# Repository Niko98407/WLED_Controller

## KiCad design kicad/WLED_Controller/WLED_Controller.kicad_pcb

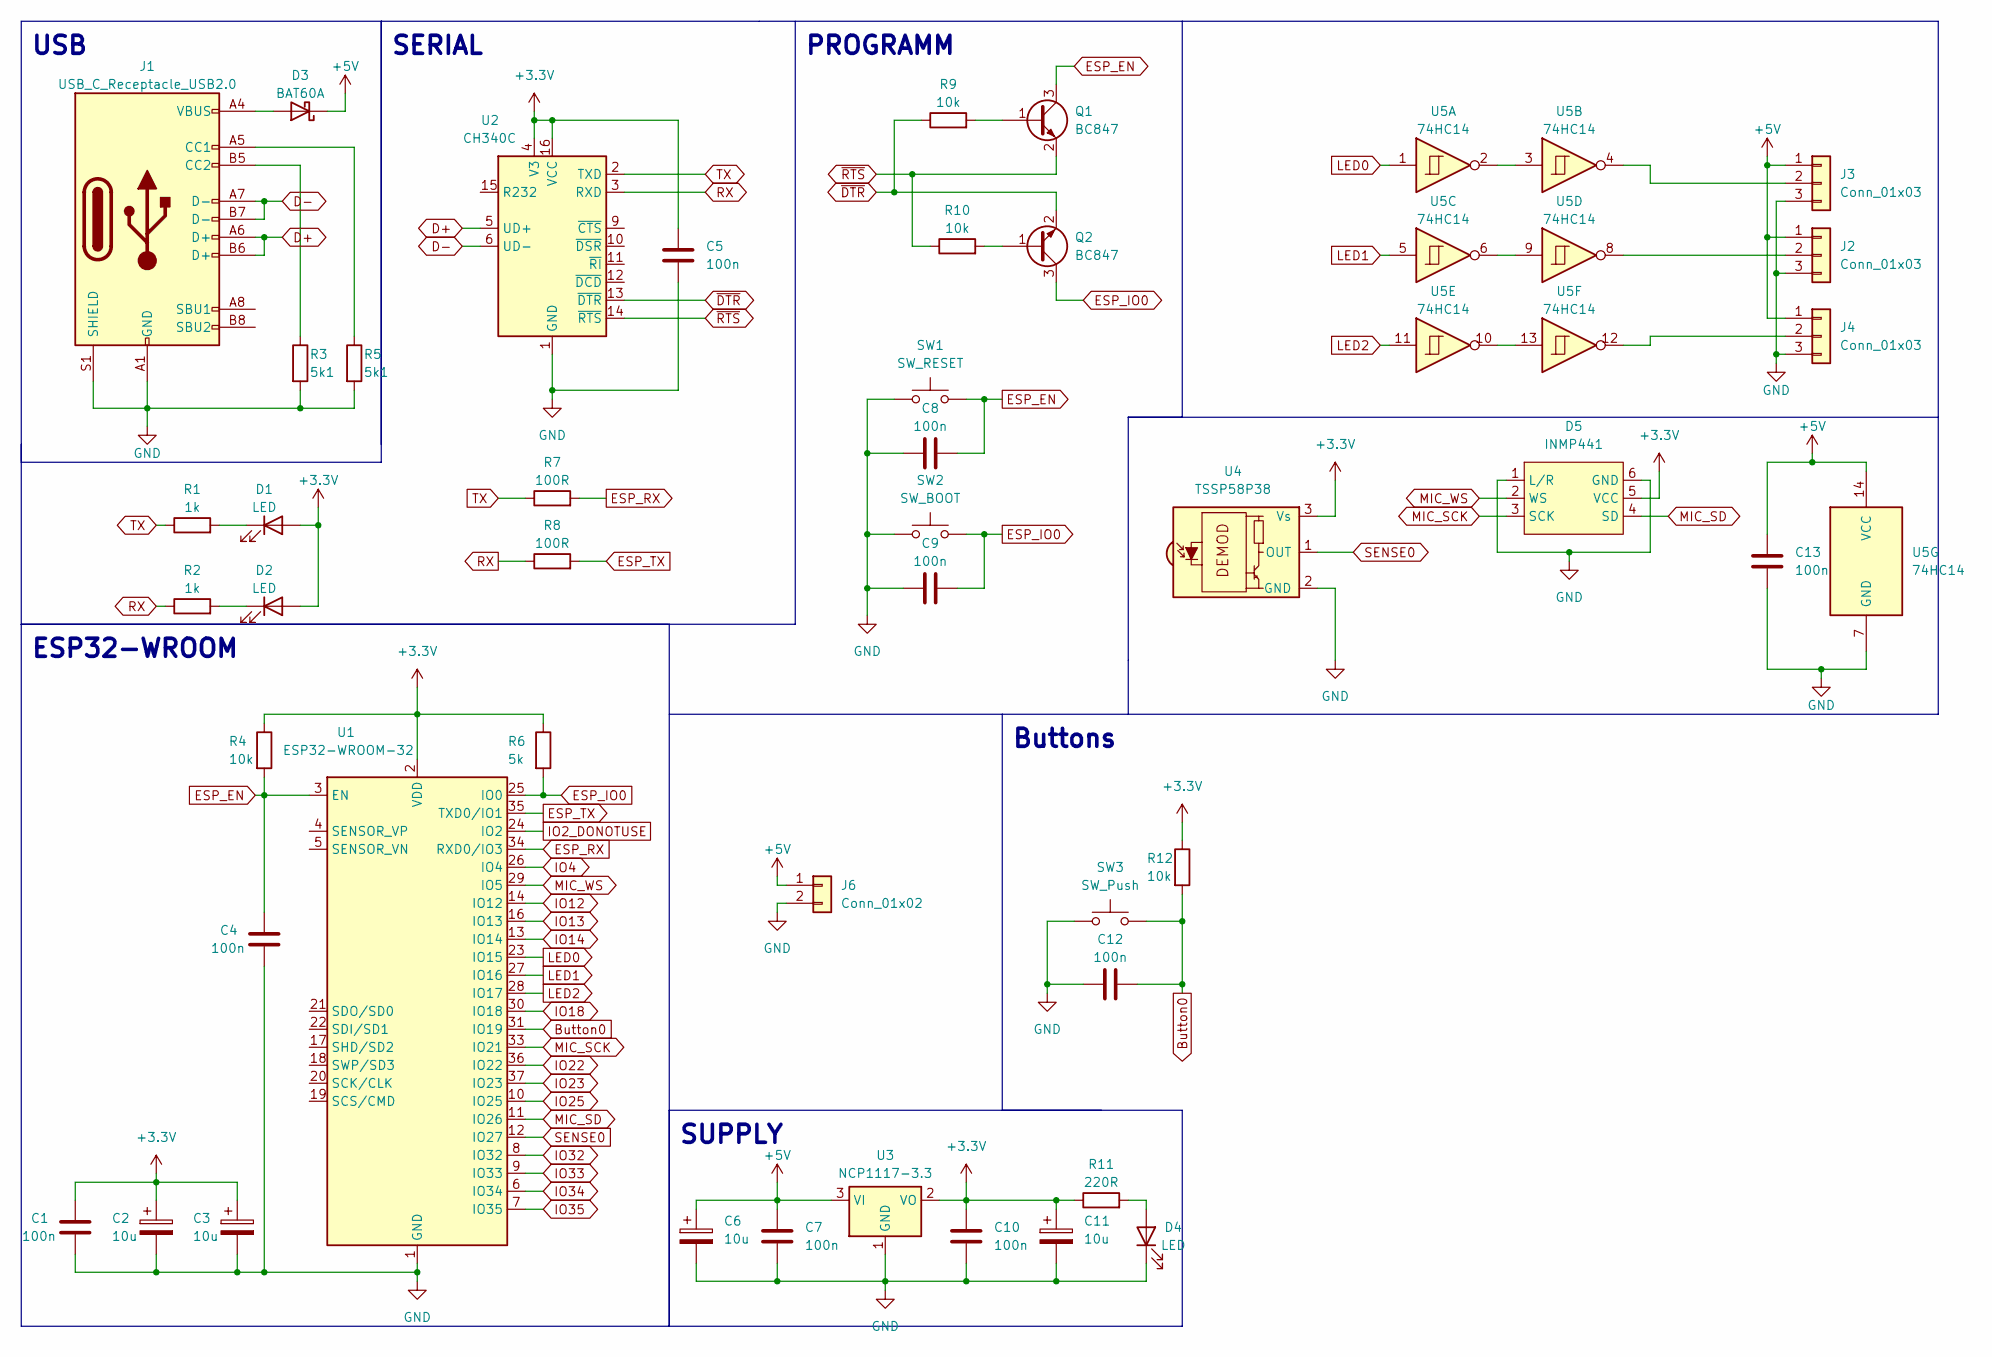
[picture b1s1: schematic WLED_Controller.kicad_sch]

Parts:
C1, C4, C5, C7, C8, C9, C10, C12, C13: 100n; C_0603_1608Metric_Pad1.08x0.95mm_HandSolder
C2, C3, C6, C11: 10u; CP_EIA-3216-18_Kemet-A_Pad1.58x1.35mm_HandSolder
D1, D2, D4: LED; LED_0603_1608Metric_Pad1.05x0.95mm_HandSolder
D3: BAT60A; D_SOD-323_HandSoldering
D5: INMP441; INMP441_Module
J1: USB_C_Receptacle_USB2.0; USB_C
J2, J3, J4: Conn_01x03; WAGO_250-203_1x03_P3.50mm
J6: Conn_01x02; WAGO_250-202_1x02_P3.50mm
Q1, Q2: BC847; SOT-23
R1, R2: 1k; R_0603_1608Metric_Pad0.98x0.95mm_HandSolder
R3, R5: 5k1; R_0603_1608Metric_Pad0.98x0.95mm_HandSolder
R4, R9, R10, R12: 10k; R_0603_1608Metric_Pad0.98x0.95mm_HandSolder
R6: 5k; R_0603_1608Metric_Pad0.98x0.95mm_HandSolder
R7, R8: 100R; R_0603_1608Metric_Pad0.98x0.95mm_HandSolder
R11: 220R; R_0603_1608Metric_Pad0.98x0.95mm_HandSolder
SW1: SW_RESET; SW_SPST_B3U-1000P
SW2: SW_BOOT; SW_SPST_B3U-1000P
SW3: SW_Push; SW_PUSH_6mm_H13mm
U1: ESP32-WROOM-32
U2: CH340C; SOIC-16_3.9x9.9mm_P1.27mm
U3: NCP1117-3.3; SOT-223-3_TabPin2
U4: TSSP58P38; TO-92L_HandSolder
U5: 74HC14; SOIC-14_3.9x8.7mm_P1.27mm

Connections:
+3.3V: C1.1, C2.1, C3.1, C5.1, C10.1, C11.1, D1.2 (A), D2.2 (A), D5.5 (VCC), R4.1, R6.1, R11.1, R12.1, U1.2 (VDD), U2.4 (V3), U2.16 (VCC), U3.2 (VO), U4.3 (Vs)
+5V: C6.1, C7.1, C13.1, D3.1 (K), J2.1, J3.1, J4.1, J6.1, U3.3 (VI), U5.14 (VCC)
Button0: C12.2, R12.2, SW3.2, U1.31 (IO19)
D+: J1.A6 (D+), J1.B6 (D+), U2.5 (UD+)
D-: J1.A7 (D-), J1.B7 (D-), U2.6 (UD-)
ESP_EN: C4.1, C8.2, Q1.3 (C), R4.2, SW1.2, U1.3 (EN)
ESP_IO0: C9.2, Q2.3 (C), R6.2, SW2.2, U1.25 (IO0)
ESP_RX: R7.2, U1.34 (RXD0/IO3)
ESP_TX: R8.2, U1.35 (TXD0/IO1)
GND: C1.2, C2.2, C3.2, C4.2, C5.2, C6.2, C7.2, C8.1, C9.1, C10.2, C11.2, C12.1, C13.2, D4.1 (K), D5.1 (L/R), D5.6 (GND), J1.A1 (GND), J1.A12 (GND), J1.B1 (GND), J1.B12 (GND), J1.S1 (SHIELD), J2.3, J3.3, J4.3, J6.2, R3.2, R5.2, SW1.1, SW2.1, SW3.1, U1.1 (GND), U1.15 (GND), U1.38 (GND), U1.39 (GND), U2.1 (GND), U3.1 (GND), U4.2 (GND), U5.7 (GND)
IO2_DONOTUSE: U1.24 (IO2)
IO4: U1.26 (IO4)
IO12: U1.14 (IO12)
IO13: U1.16 (IO13)
IO14: U1.13 (IO14)
IO18: U1.30 (IO18)
IO22: U1.36 (IO22)
IO23: U1.37 (IO23)
IO25: U1.10 (IO25)
IO32: U1.8 (IO32)
IO33: U1.9 (IO33)
IO34: U1.6 (IO34)
IO35: U1.7 (IO35)
LED0: U1.23 (IO15), U5.1
LED1: U1.27 (IO16), U5.5
LED2: U1.28 (IO17), U5.11
MIC_SCK: D5.3 (SCK), U1.33 (IO21)
MIC_SD: D5.4 (SD), U1.11 (IO26)
MIC_WS: D5.2 (WS), U1.29 (IO5)
unnamed: D1.1 (K), R1.2
unnamed: D2.1 (K), R2.2
unnamed: D3.2 (A), J1.A4 (VBUS), J1.A9 (VBUS), J1.B4 (VBUS), J1.B9 (VBUS)
unnamed: D4.2 (A), R11.2
unnamed: J1.A5 (CC1), R5.1
unnamed: J1.B5 (CC2), R3.1
unnamed: J2.2, U5.8
unnamed: J3.2, U5.4
unnamed: J4.2, U5.12
unnamed: Q1.1 (B), R9.2
unnamed: Q2.1 (B), R10.2
unnamed: U5.2, U5.3
unnamed: U5.6, U5.9
unnamed: U5.10, U5.13
RX: R2.1, R8.1, U2.3 (RXD)
SENSE0: U1.12 (IO27), U4.1 (OUT)
TX: R1.1, R7.1, U2.2 (TXD)
~DTR: Q2.2 (E), R9.1, U2.13 (~DTR)
~RTS: Q1.2 (E), R10.1, U2.14 (~RTS)

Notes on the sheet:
USB
SERIAL
ESP32-WROOM
PROGRAMM
Buttons
SUPPLY

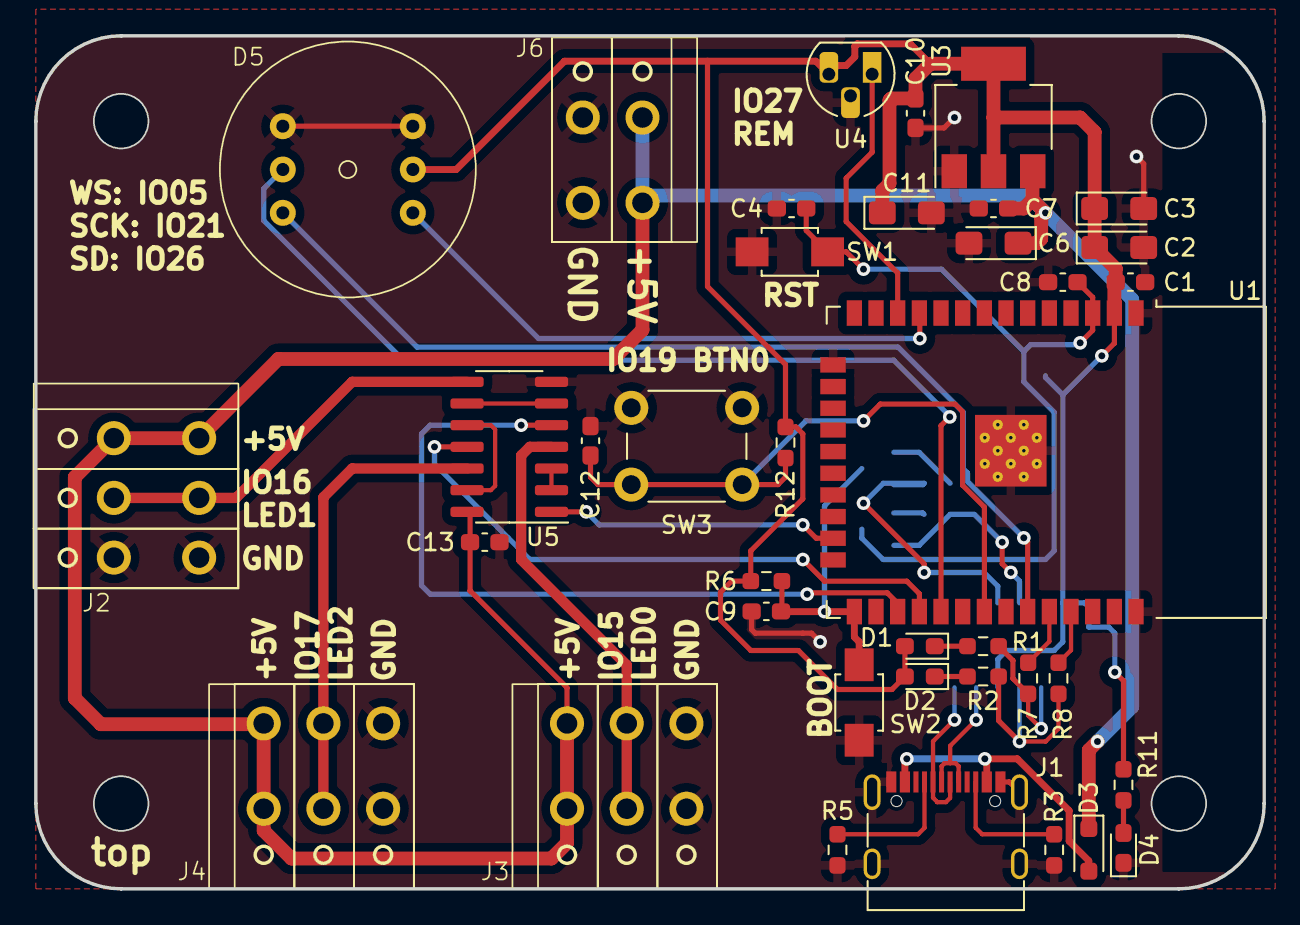
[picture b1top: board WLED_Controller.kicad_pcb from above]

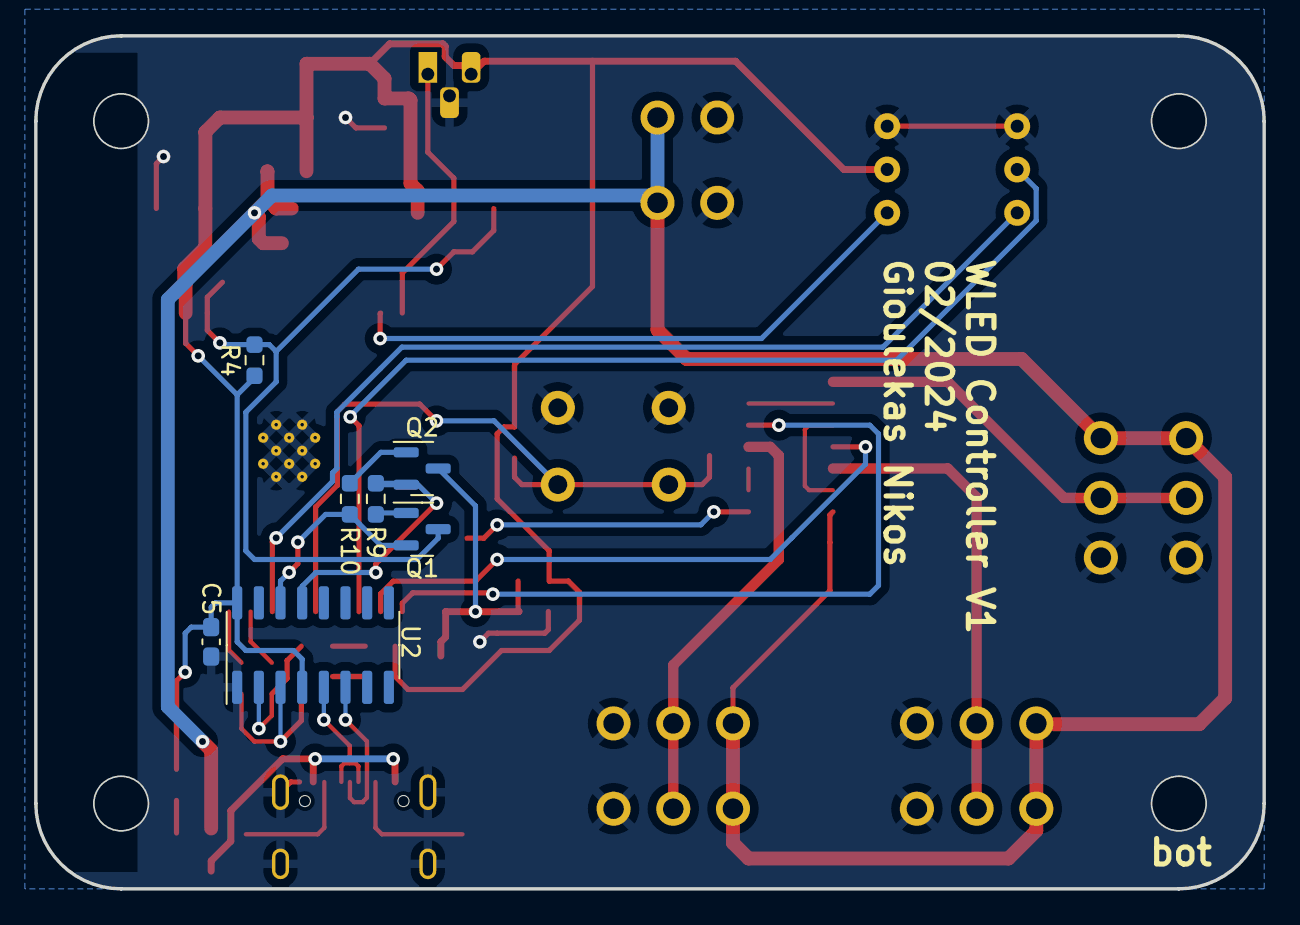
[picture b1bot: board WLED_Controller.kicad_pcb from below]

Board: 2 copper layers, 72.0 x 50.0 mm, 45 parts (7 on the bottom side), 35 nets.

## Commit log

2024-02-17 add Project
2024-02-18 begin creating schematic
2024-02-21 add Microphone
2024-02-23 Add V1
2024-04-28 Change to WAGO250
